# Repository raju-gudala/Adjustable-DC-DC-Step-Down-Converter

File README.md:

# Adjustable DC-DC Step-Down Converter

This project demonstrates the design and implementation of an adjustable DC-DC buck converter using the **LM2596S-ADJ** IC. The converter accepts a wide input range of **4.5–40V DC** and delivers a regulated, adjustable output capable of supplying up to **3A** continuous current.

## Features

- Complete schematic design in KiCad
- LTspice simulation for stability and performance verification
- Optimized PCB layout for high efficiency and low output ripple
- Power stage, feedback network, and input/output filtering included
- Reliable voltage regulation using feedback compensation techniques

## Specifications

| Parameter | Value |
|---|---|
| IC | LM2596S-ADJ |
| Input Voltage | 5V – 40V DC |
| Output Voltage | Adjustable |
| Max Output Current | 3A (continuous) |
| Topology | Step-down (Buck) |

## Repository Contents

```
├── KiCad/          # Schematic and PCB layout files
├── LTspice/        # Simulation files for stability and performance analysis
└── README.md
```

## Design Overview

The converter is built around the LM2596S-ADJ switching regulator, configured with an external feedback resistor divider to allow adjustable output voltage. The design includes:

- **Power stage** — inductor, diode, and switching components sized for target load current
- **Feedback network** — resistor divider with compensation for stable regulation across the input range
- **Input/output filtering** — capacitor selection for ripple reduction and stability margin

## Simulation

LTspice simulations were used to verify loop stability and steady-state performance prior to PCB fabrication, validating transient response and output ripple against the design targets.

## PCB Layout

The PCB layout follows standard buck converter layout guidelines — minimized switching node area, tight power loop, and proper ground return paths — to reduce EMI and ripple while maximizing conversion efficiency.

## Tools Used

- **KiCad** — Schematic capture and PCB design
- **LTspice** — Circuit simulation and stability analysis

## License

Feel free to specify a license (e.g., MIT) if you'd like others to reuse this design.

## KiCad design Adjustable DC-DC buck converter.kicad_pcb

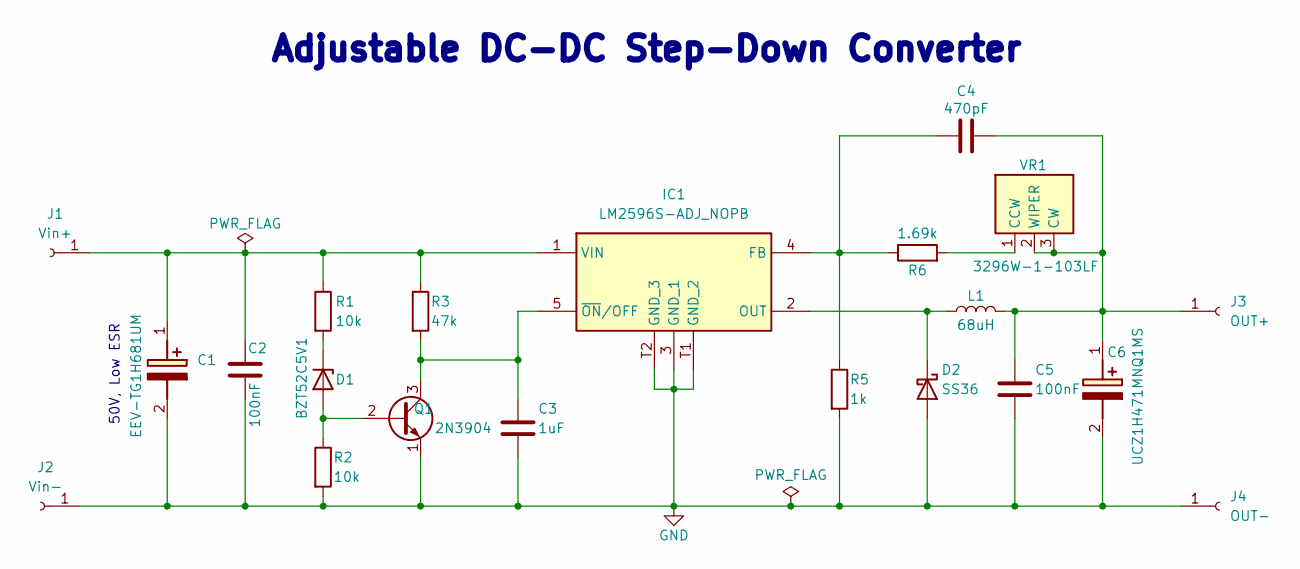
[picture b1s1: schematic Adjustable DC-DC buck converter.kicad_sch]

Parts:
C1: EEV-TG1H681UM; CAPAE1700X1700N; Mouser Part Number 667-EEV-TG1H681UM
C2: 100nF; C_0805_2012Metric
C3: 1uF; C_0805_2012Metric
C4: 470pF; C_0603_1608Metric
C5: 100nF; C_0603_1608Metric
C6: UCZ1H471MNQ1MS; CAPAE1710X1750N; Mouser Part Number 667-EEE-FK1H471AM
D1: BZT52C5V1; D_SOD-123F
D2: SS36; D_SMA
IC1: LM2596S-ADJ_NOPB; LM2596SXADJ; Mouser Part Number 926-LM2596S-ADJ/NOPB
J1: Vin+; SolderWire-2.5sqmm_1x01_D2.4mm_OD4.4mm
J2: Vin-; SolderWire-2.5sqmm_1x01_D2.4mm_OD4.4mm
J3: OUT+; SolderWire-2.5sqmm_1x01_D2.4mm_OD4.4mm
J4: OUT-; SolderWire-2.5sqmm_1x01_D2.4mm_OD4.4mm
L1: 68uH; L_0603_1608Metric
Q1: 2N3904; TO-92_Inline
R1, R2: 10k; R_0603_1608Metric
R3: 47k; R_0603_1608Metric
R5: 1k; R_0603_1608Metric
R6: 1.69k; R_0603_1608Metric
VR1: 3296W-1-103LF; 3296W1503LF; Mouser Part Number 652-3296W-1-103LF

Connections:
GND: C1.2 (-), C2.2, C3.2, C5.2, C6.2 (-), D2.2 (A), IC1.3 (GND_1), IC1.T1 (GND_2), IC1.T2 (GND_3), J2.1 (Pin_1_1), J4.1 (Pin_1_1), Q1.1 (E), R2.2, R5.2
unnamed: C1.1 (+), C2.1, IC1.1 (VIN), J1.1 (Pin_1_1), R1.1, R3.1
unnamed: C4.2, C5.1, C6.1 (+), J3.1 (Pin_1_1), L1.2, VR1.2 (WIPER), VR1.3 (CW)
unnamed: D1.2 (A), Q1.2 (B), R2.1
unnamed: D1.1 (K), R1.2
unnamed: D2.1 (K), IC1.2 (OUT), L1.1
unnamed: C4.1, IC1.4 (FB), R5.1, R6.1
unnamed: C3.1, IC1.5 (~ON/OFF), Q1.3 (C), R3.2
unnamed: R6.2, VR1.1 (CCW)

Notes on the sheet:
50V, Low ESR
Adjustable DC-DC Step-Down Converter

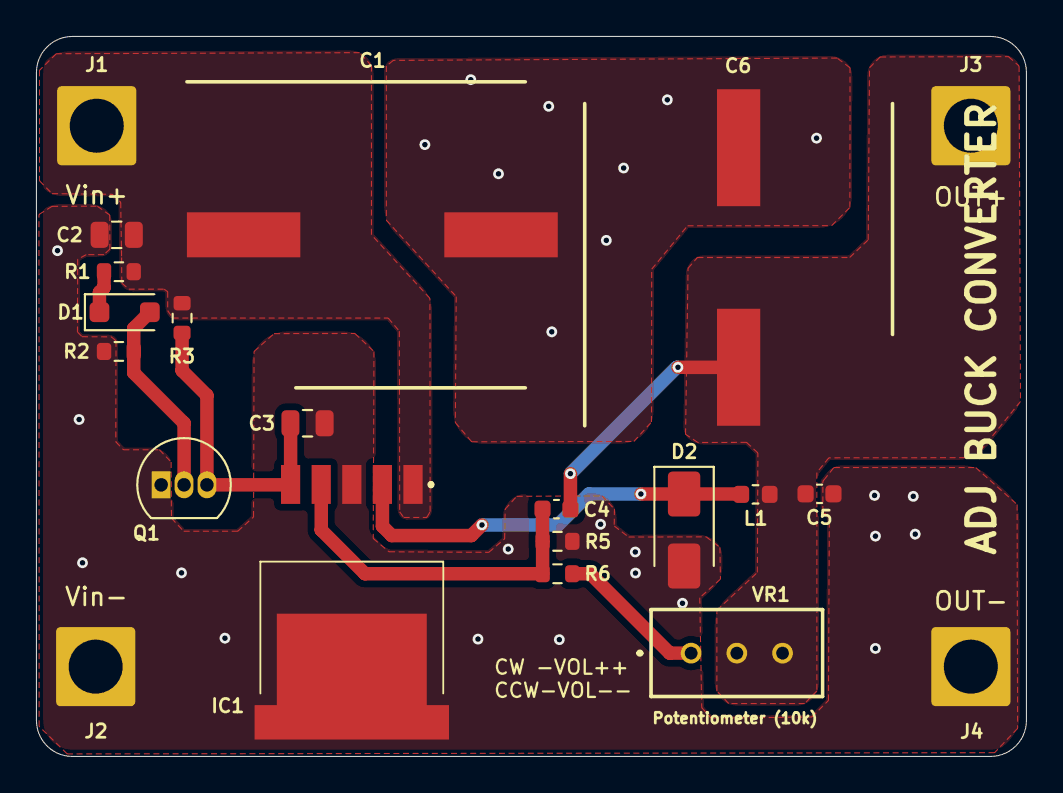
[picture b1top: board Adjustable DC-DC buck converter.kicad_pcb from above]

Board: 2 copper layers, 55.0 x 40.0 mm, 21 parts (0 on the bottom side), 9 nets.
